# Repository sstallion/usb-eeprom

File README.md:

# 28Cxxx EEPROM Programmer

This repository contains the firmware and hardware design for a PIC18F-based
USB programmer for the 28Cxxx series of parallel EEPROMs.

This project meets the requirements of the [OSHW Definition][1]. CadSoft EAGLE
design files and an example bill of materials can be found in the [eagle]
directory. For those without access to EAGLE, a PDF of the schematic and board
layout is provided.

PCBs may be ordered from [OSH Park][2]. Fully assembled and tested units may
also be purchased from [Tindie][3].

## Firmware

The firmware requires the Microchip MPLAB XC8 compiler and the MPLAB X IPE
(Integrated Programming Environment) be installed and added to the user's PATH.

To build the firmware, issue:

    $ make all

To program the firmware using an attached MPLAB PICkit 3, issue:

    $ make run

Other programmers may be used; see `Makefile` for more detail.

## Usage

A cross-platform command line tool was developed to drive the programmer,
written in Go. Installing the `eeprom` tool requires Go 1.2 and libusb 1.0; see
[Getting Started][4] for more details.

To install the `eeprom` tool, issue:

    $ go get github.com/sstallion/go-eeprom/cmd/eeprom

Once installed, issue `eeprom help` to display usage.

## Compatibility

All 5V single supply chips are supported for read and write operations.
Extended functionality, such as page writes and chip erase are supported for
Atmel AT28C and compatible families.

_High-voltage programming is not supported._

## Contributing

Pull requests are welcome! If a problem is encountered using this repository,
please file an issue on [GitHub][5].

## License

Source code in this repository is licensed under a Simplified BSD License with
additional restrictions. See [LICENSE] and [LICENSE-MLA] for more details.

[1]: https://www.oshwa.org/definition/
[2]: http://oshpark.com/shared_projects/PVCsM6xC
[3]: https://www.tindie.com/products/sstallion/28cxxx-eeprom-programmer
[4]: http://golang.org/doc/install
[5]: https://github.com/sstallion/usb-eeprom/issues

[LICENSE]: LICENSE
[LICENSE-MLA]: LICENSE-MLA
[eagle]: eagle

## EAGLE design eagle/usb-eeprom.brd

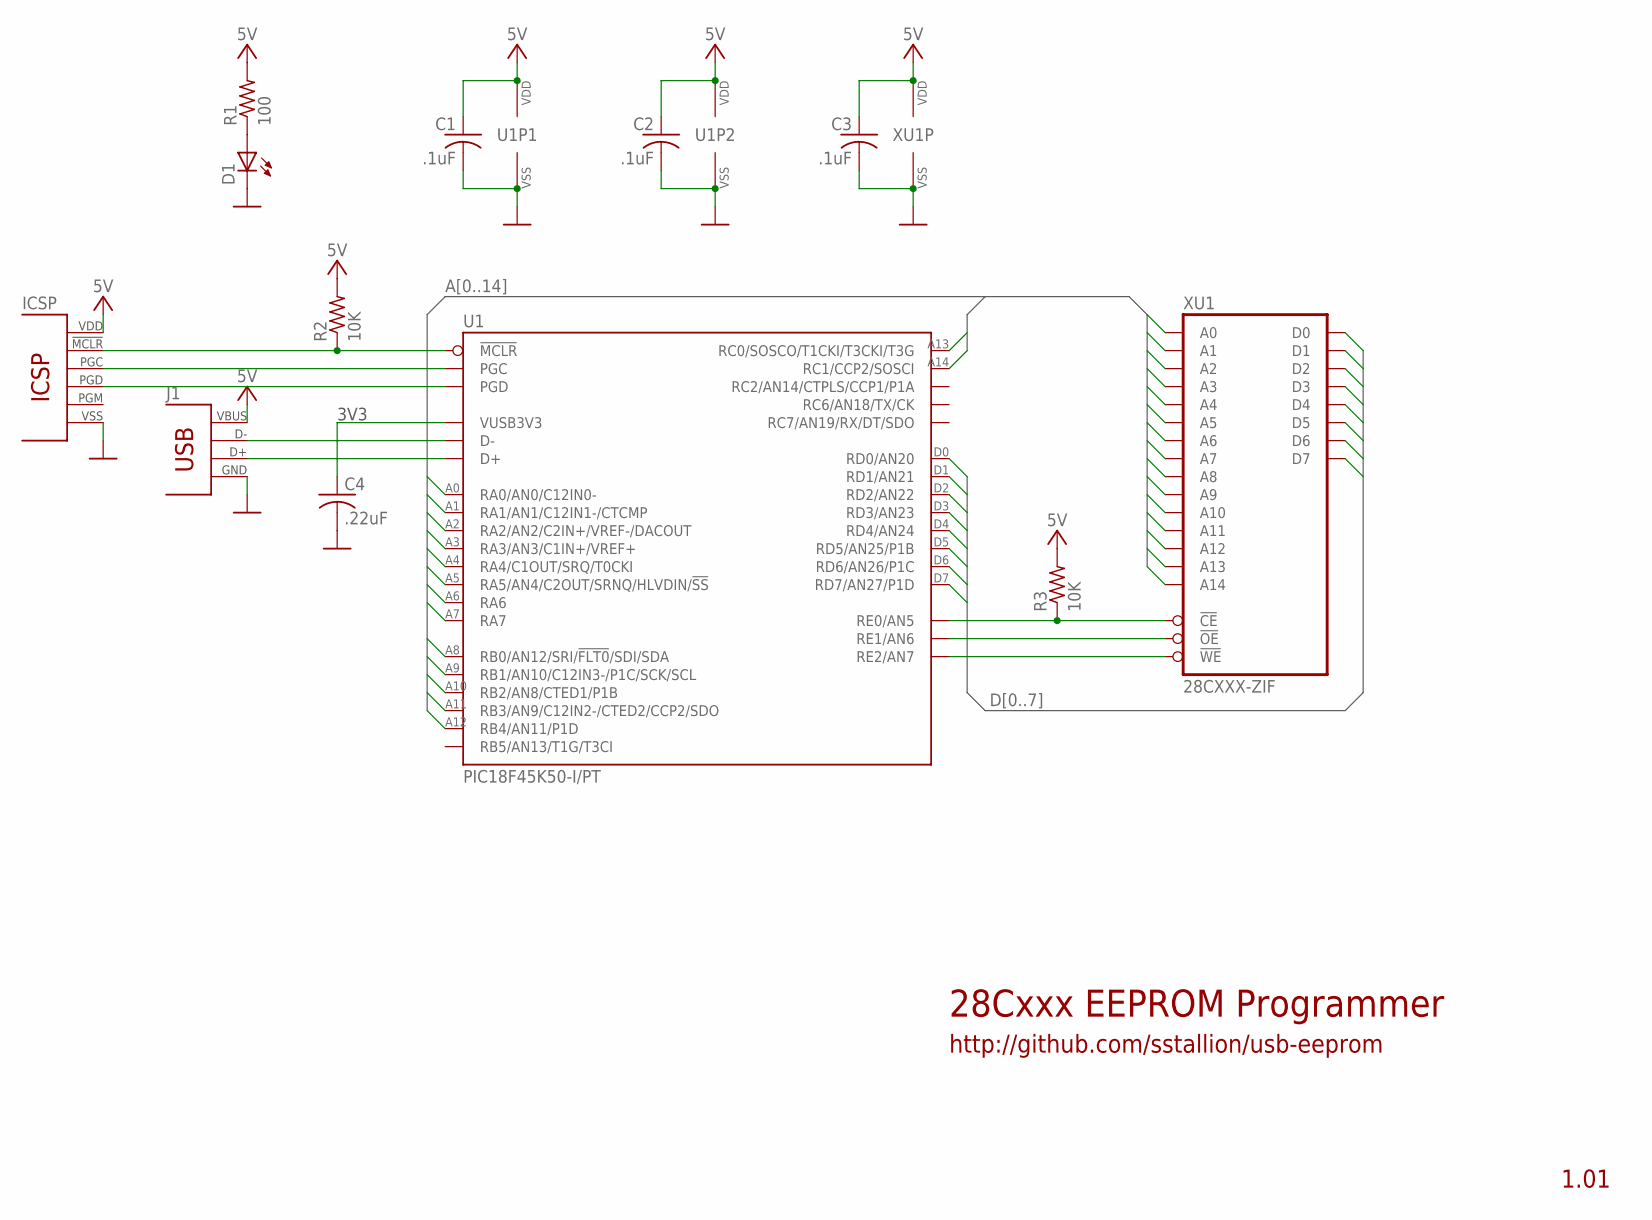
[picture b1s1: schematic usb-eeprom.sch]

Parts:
C1, C2, C3: .1uF; C0805; MFG_PN VJ0805Y104KXJCW1BC; MOUSER_PN 77-VJ0805Y104KXJCBC
C4: .22uF; C0805; MFG_PN VJ0805Y224KXJTW1BC; MOUSER_PN 77-VJ0805Y224KXJTBC
D1: BLUE; SML0805; MFG_PN APT2012QBC/D; MOUSER_PN 604-APT2012QBC/D
ICSP: ICSP
J1: USBA; MFG_PN 48037-0001; MOUSER_PN 538-48037-0001
R1: 100; R0805; MFG_PN CRCW0805100RFKEA; MOUSER_PN 71-CRCW0805-100-E3
R2, R3: 10K; R0805; MFG_PN CRCW080510K0FKEB; MOUSER_PN 71-CRCW080510K0FKEB
U1: PIC18F45K50-I/PT; TQFP44; MFG_PN PIC18F45K50-I/PT; MOUSER_PN 579-PIC18F45K50-I/PT
XU1: 28CXXX-ZIF; ZIF28; MFG_PN 228-1371-00-0602J; MOUSER_PN 517-228-1371-00

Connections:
+5V: C1.1, C2.1, C3.1, ICSP.2 (VDD), J1.1, R1.2, R2.2, R3.2, U1.7 (VDD), U1.28 (VDD), XU1.28 (VDD)
A0: U1.19 (RA0/AN0/C12IN0-), XU1.10 (A0)
A1: U1.20 (RA1/AN1/C12IN1-/CTCMP), XU1.9 (A1)
A2: U1.21 (RA2/AN2/C2IN+/VREF-/DACOUT), XU1.8 (A2)
A3: U1.22 (RA3/AN3/C1IN+/VREF+), XU1.7 (A3)
A4: U1.23 (RA4/C1OUT/SRQ/T0CKI), XU1.6 (A4)
A5: U1.24 (RA5/AN4/C2OUT/SRNQ/HLVDIN/!SS!), XU1.5 (A5)
A6: U1.31 (RA6), XU1.4 (A6)
A7: U1.30 (RA7), XU1.3 (A7)
A8: U1.8 (RB0/AN12/SRI/!FLT0!/SDI/SDA), XU1.25 (A8)
A9: U1.9 (RB1/AN10/C12IN3-/P1C/SCK/SCL), XU1.24 (A9)
A10: U1.10 (RB2/AN8/CTED1/P1B), XU1.21 (A10)
A11: U1.11 (RB3/AN9/C12IN2-/CTED2/CCP2/SDO), XU1.23 (A11)
A12: U1.14 (RB4/AN11/P1D), XU1.2 (A12)
A13: U1.32 (RC0/SOSCO/T1CKI/T3CKI/T3G), XU1.26 (A13)
A14: U1.35 (RC1/CCP2/SOSCI), XU1.1 (A14)
D0: U1.38 (RD0/AN20), XU1.11 (D0)
D1: U1.39 (RD1/AN21), XU1.12 (D1)
D2: U1.40 (RD2/AN22), XU1.13 (D2)
D3: U1.41 (RD3/AN23), XU1.15 (D3)
D4: U1.2 (RD4/AN24), XU1.16 (D4)
D5: U1.3 (RD5/AN25/P1B), XU1.17 (D5)
D6: U1.4 (RD6/AN26/P1C), XU1.18 (D6)
D7: U1.5 (RD7/AN27/P1D), XU1.19 (D7)
GND: C1.2, C2.2, C3.2, C4.2, D1.C, ICSP.3 (VSS), J1.4, J1.5 (4), J1.6 (4), U1.6 (VSS), U1.29 (VSS), XU1.14 (VSS)
unnamed: ICSP.1 (!MCLR), R2.1, U1.18 (!MCLR)
unnamed: ICSP.5 (PGC), U1.16 (PGC)
unnamed: ICSP.4 (PGD), U1.17 (PGD)
unnamed: C4.1, U1.37 (VUSB3V3)
unnamed: R3.1, U1.25 (RE0/AN5), XU1.20 (!CE)
unnamed: J1.2, U1.42 (D-)
unnamed: J1.3, U1.43 (D+)
unnamed: U1.26 (RE1/AN6), XU1.22 (!OE)
unnamed: U1.27 (RE2/AN7), XU1.27 (!WE)
unnamed: D1.A, R1.1

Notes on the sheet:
28Cxxx EEPROM Programmer
http://github.com/sstallion/usb-eeprom
3V3

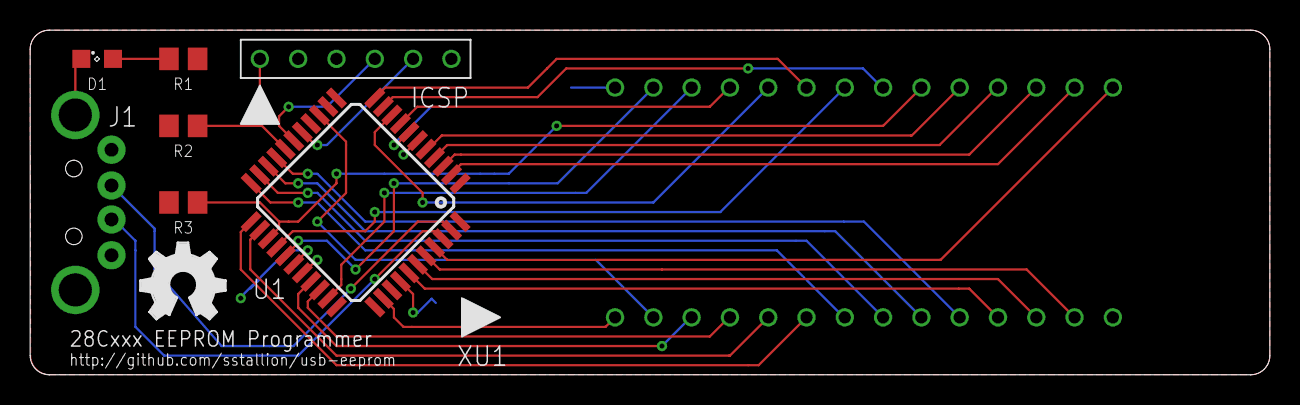
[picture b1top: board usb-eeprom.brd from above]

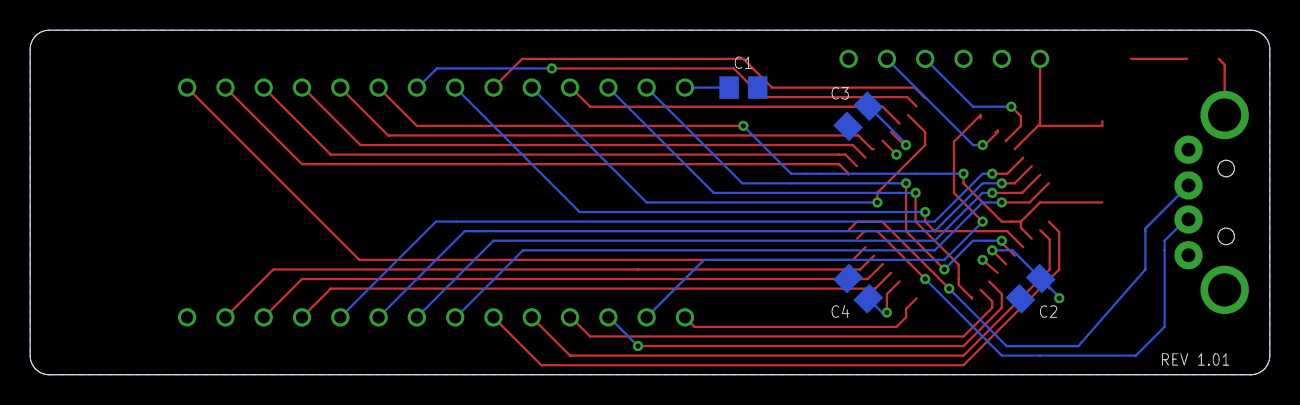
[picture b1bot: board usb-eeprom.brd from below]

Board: 2 copper layers, 82.2 x 22.9 mm, 13 parts (4 on the bottom side), 35 nets.

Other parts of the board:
LOGO: OSHW

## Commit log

2014-05-15 Update product string
2014-05-15 Initialize EAGLE project
2014-05-15 Update product/manufacturer string length
2014-05-15 Update DEVICE/PROGRAMMER
2014-05-15 Add PIC18(L)F45K50 symbol
2014-05-16 Add remaining symbols/packages
2014-05-17 Update schematic; generate BOM
2014-05-17 Update LATE operations for consistency
2014-05-20 Initial PCB layout
2014-05-20 Update to official PID
2014-05-20 Add usb-eeprom-board.pdf
2014-05-20 Rename PDF files
2014-05-23 Fix page addressing; disable WDT
2014-05-23 Update BOM
2014-05-23 Fix broken addressing (really)
2014-05-24 Fix warning 1311 (unset CONFIG2L)
2014-05-24 Replace D1 with SML0805 package
2014-05-26 Move PDFs to wiki
2014-05-26 Update documentation
2014-05-29 Robustificate USB handling
2014-05-29 Add support for !DATA polling
2014-05-29 Move Protocol/Performance to wiki
2014-05-31 Unite PDFs
2014-06-03 Update bcdDevice
2014-06-03 Cosmetic fixes; REV 1.01 layout
2014-07-13 Upgrade to EAGLE v6.6; update formatting
2015-06-22 Correct bad addr assignment in Chip Erase
2017-12-31 First round of updates for next release
2018-10-13 Update LICENSE
2019-06-20 Update eeprom command location
